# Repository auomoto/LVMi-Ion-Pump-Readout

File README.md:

# LVMi-Ion-Pump-Readout
 Reads out three Modion Ion Pumps

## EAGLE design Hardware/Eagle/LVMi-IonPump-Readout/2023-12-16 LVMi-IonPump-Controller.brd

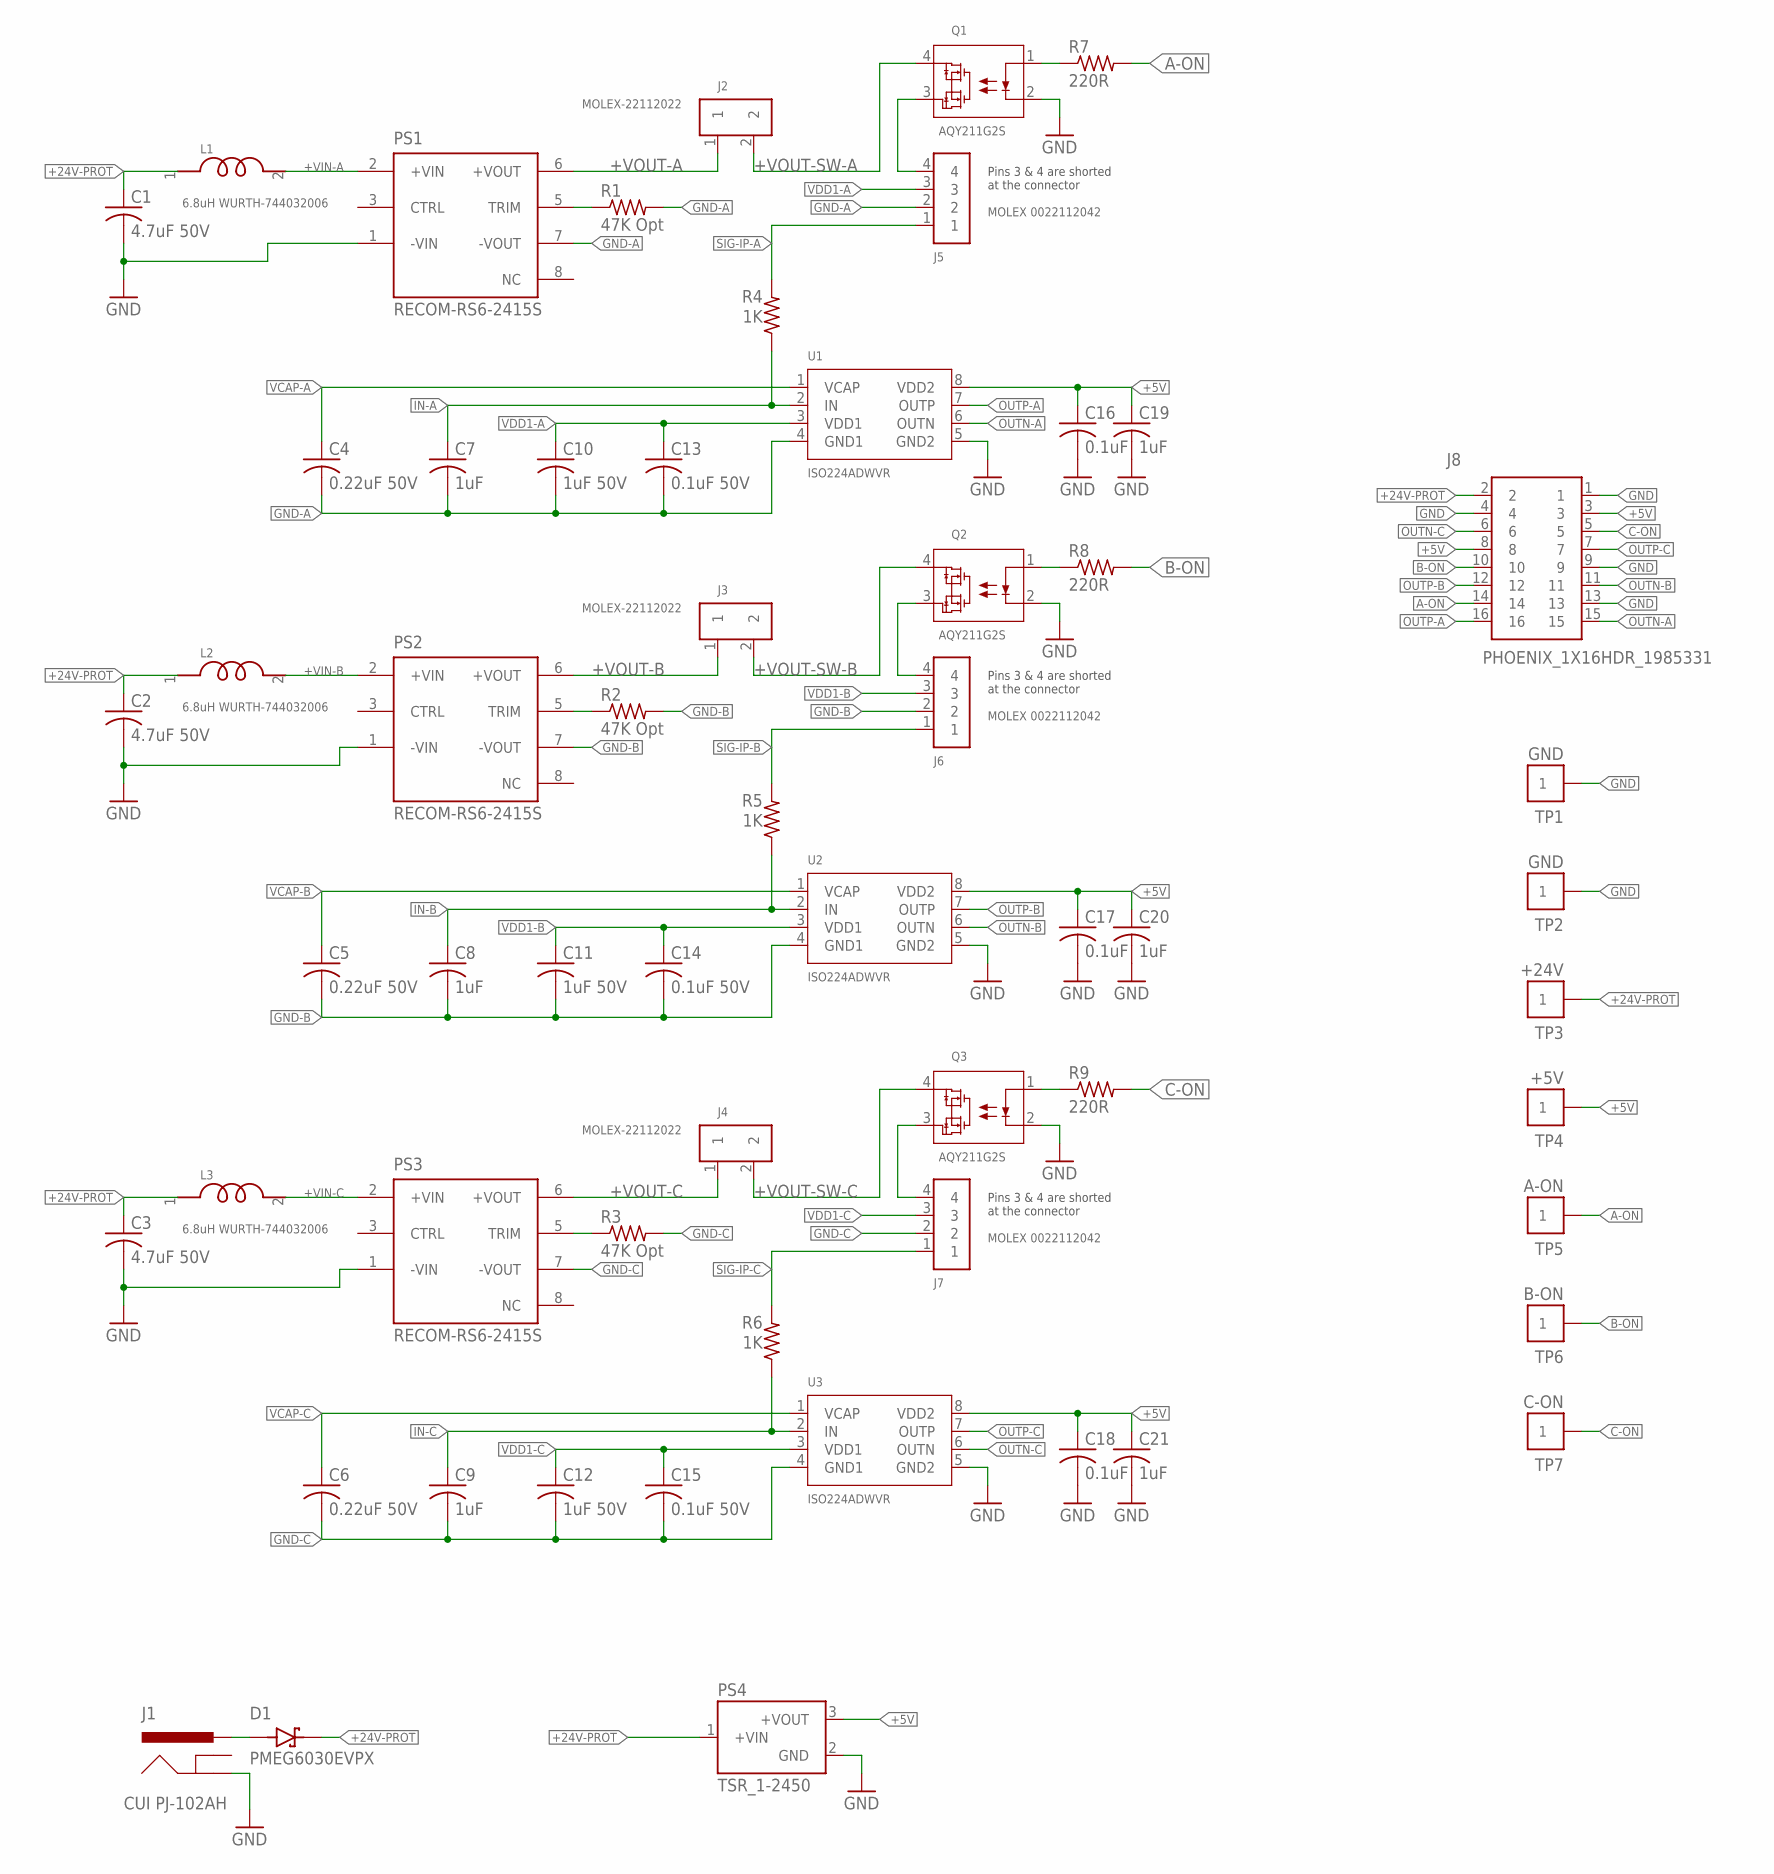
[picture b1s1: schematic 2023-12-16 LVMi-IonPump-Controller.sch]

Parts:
C1, C2, C3: 4.7uF 50V; C0805
C4, C5, C6: 0.22uF 50V; C0805
C7, C8, C9, C19, C20, C21: 1uF; C0805
C10, C11, C12: 1uF 50V; C0805
C13, C14, C15: 0.1uF 50V; C0805
C16, C17, C18: 0.1uF; C0805
D1: PMEG6030EVPX; DIO_PMEG6030EVPX
J1: CUI PJ-102AH; PJ-102AH
J2, J3, J4: MOLEX-22112022; 1X02-MOLEX-22112022
J5, J6, J7: MOLEX 0022112042; 1X04-MOLEX-22112042
J8: PHOENIX_1X16HDR_1985331; 1985331
L1, L2, L3: 6.8uH WURTH-744032006; WURTH-1210-INDUCTOR
PS1, PS2, PS3: RECOM-RS6-2415S; CONV_RS6-2415S
PS4: TSR_1-2450; CONV_TSR_1-2450
Q1, Q2, Q3: AQY211G2S; SOP4_PAN
R1, R2, R3: 47K Opt; R0805
R4, R5, R6: 1K; R0805
R7, R8, R9: 220R; R0805
TP1, TP2: GND; TP5000-TESTPOINT-BLK
TP3: +24V; TP5000-TESTPOINT-BLK
TP4: +5V; TP5000-TESTPOINT-BLK
TP5: A-ON; TP5000-TESTPOINT-BLK
TP6: B-ON; TP5000-TESTPOINT-BLK
TP7: C-ON; TP5000-TESTPOINT-BLK
U1, U2, U3: ISO224ADWVR; DWV8_TEX

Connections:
+5V: C16.1, C17.1, C18.1, C19.1, C20.1, C21.1, J8.3, J8.8, PS4.3 (+VOUT), TP4.P$1, U1.8 (VDD2), U2.8 (VDD2), U3.8 (VDD2)
+24V: D1.2 (A), J1.PWR
+24V-PROT: C1.1, C2.1, C3.1, D1.1 (K), J8.2, L1.1, L2.1, L3.1, PS4.1 (+VIN), TP3.P$1
+VIN-A: L1.2, PS1.2 (+VIN)
+VIN-B: L2.2, PS2.2 (+VIN)
+VIN-C: L3.2, PS3.2 (+VIN)
+VOUT-A: J2.1, PS1.6 (+VOUT)
+VOUT-B: J3.1, PS2.6 (+VOUT)
+VOUT-C: J4.1, PS3.6 (+VOUT)
+VOUT-SW-A: J2.2, Q1.4
+VOUT-SW-B: J3.2, Q2.4
+VOUT-SW-C: J4.2, Q3.4
A-ON: J8.14, R7.2, TP5.P$1
B-ON: J8.10, R8.2, TP6.P$1
C-ON: J8.5, R9.2, TP7.P$1
GND: C1.2, C2.2, C3.2, C16.2, C17.2, C18.2, C19.2, C20.2, C21.2, J1.GND, J8.1, J8.4, J8.9, J8.13, PS1.1 (-VIN), PS2.1 (-VIN), PS3.1 (-VIN), PS4.2 (GND), Q1.2, Q2.2, Q3.2, TP1.P$1, TP2.P$1, U1.5 (GND2), U2.5 (GND2), U3.5 (GND2)
GND-A: C4.2, C7.2, C10.2, C13.2, J5.2, PS1.7 (-VOUT), R1.2, U1.4 (GND1)
GND-B: C5.2, C8.2, C11.2, C14.2, J6.2, PS2.7 (-VOUT), R2.2, U2.4 (GND1)
GND-C: C6.2, C9.2, C12.2, C15.2, J7.2, PS3.7 (-VOUT), R3.2, U3.4 (GND1)
IN-A: C7.1, R4.1, U1.2 (IN)
IN-B: C8.1, R5.1, U2.2 (IN)
IN-C: C9.1, R6.1, U3.2 (IN)
unnamed: Q3.1, R9.1
unnamed: Q1.1, R7.1
unnamed: Q2.1, R8.1
unnamed: PS3.5 (TRIM), R3.1
unnamed: PS2.5 (TRIM), R2.1
unnamed: PS1.5 (TRIM), R1.1
OUTN-A: J8.15, U1.6 (OUTN)
OUTN-B: J8.11, U2.6 (OUTN)
OUTN-C: J8.6, U3.6 (OUTN)
OUTP-A: J8.16, U1.7 (OUTP)
OUTP-B: J8.12, U2.7 (OUTP)
OUTP-C: J8.7, U3.7 (OUTP)
SIG-IP-A: J5.1, R4.2
SIG-IP-B: J6.1, R5.2
SIG-IP-C: J7.1, R6.2
VCAP-A: C4.1, U1.1 (VCAP)
VCAP-B: C5.1, U2.1 (VCAP)
VCAP-C: C6.1, U3.1 (VCAP)
VDD1-A: C10.1, C13.1, J5.3, U1.3 (VDD1)
VDD1-B: C11.1, C14.1, J6.3, U2.3 (VDD1)
VDD1-C: C12.1, C15.1, J7.3, U3.3 (VDD1)
VOUT-RL-A: J5.4, Q1.3
VOUT-RL-B: J6.4, Q2.3
VOUT-RL-C: J7.4, Q3.3

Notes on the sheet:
Pins 3 & 4 are shorted at the connector

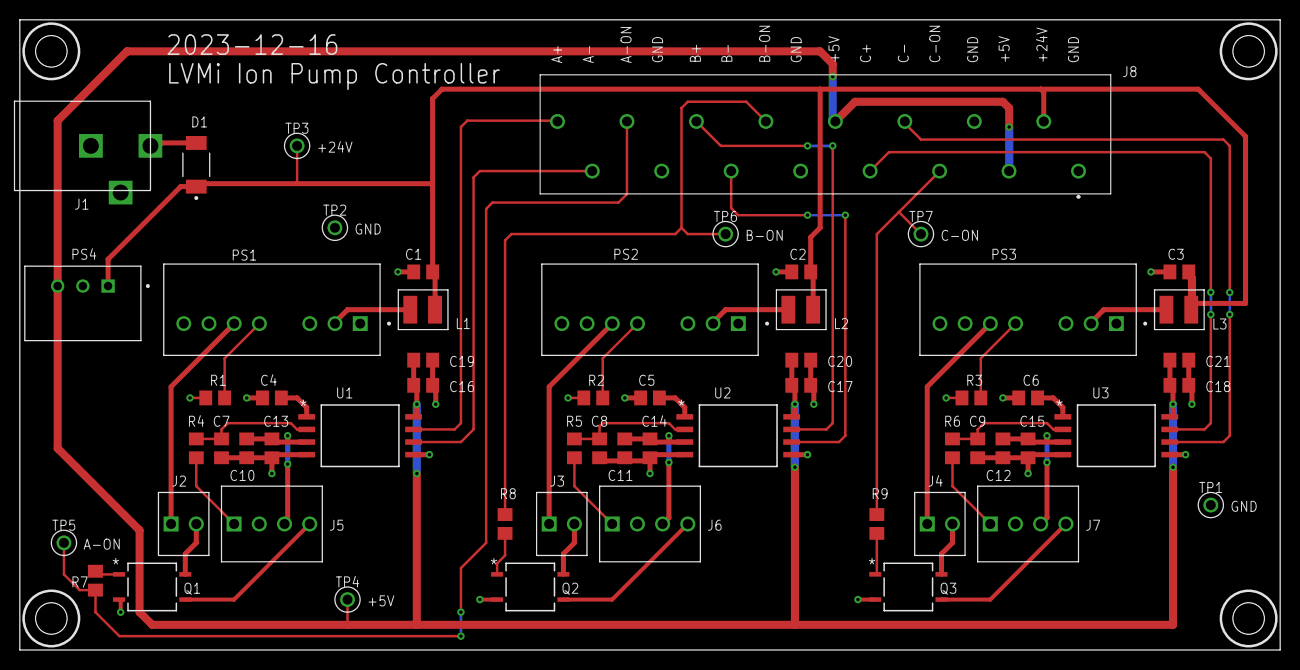
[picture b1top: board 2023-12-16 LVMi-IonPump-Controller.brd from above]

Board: 2 copper layers, 127.0 x 63.5 mm, 59 parts (0 on the bottom side), 46 nets.

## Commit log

2024-01-11 Added hardware directory
2024-01-14 Updated opto current resistor to 220R

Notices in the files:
parts and their libraries:
COPYRIGHT: Copyright (C) 2018 Accelerated Designs. All rights reserved
COPYRIGHT: Copyright (C) 2023 Ultra Librarian. All rights reserved.
